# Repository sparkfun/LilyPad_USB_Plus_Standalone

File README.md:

SparkFun LilyPad USB Plus
========================================

[*LilyPad USB Plus (14631)*](https://www.sparkfun.com/products/14631)

This is the LilyPad USB Plus, a sewable electronics microcontroller board controlled by an ATmega32U4 with the Arduino bootloader. 

Repository Contents
-------------------

* **/Documentation** - Data sheets, additional product information
* **/Hardware** - Eagle design files (.brd, .sch)
* **/Production** - Production panel files (.brd)

<b>Note for Linux Users:</b> If you are installing the LilyPad USB Plus in Linux, this document has some specific notes:
<a href="https://github.com/sparkfun/LilyPad_ProtoSnap_Plus/blob/master/Documentation/LinuxInstallation.md">https://github.com/sparkfun/LilyPad_ProtoSnap_Plus/blob/master/Documentation/LinuxInstallation.md</a>.

Documentation
--------------
* **[Library](https://github.com/sparkfun/LilyPad_USB_Plus_Standalone/tree/master/Libraries)** - Arduino library for the LilyPad USB Plus.
* **[Hookup Guide](https://learn.sparkfun.com/tutorials/lilypad-usb-plus-hookup-guide)** - Basic hookup guide for the LilyPad USB Plus.

License Information
-------------------

This product is _**open source**_! 

Please review the LICENSE.md file for license information. 

If you have any questions or concerns on licensing, please contact techsupport@sparkfun.com.

Distributed as-is; no warranty is given.

- Your friends at SparkFun.

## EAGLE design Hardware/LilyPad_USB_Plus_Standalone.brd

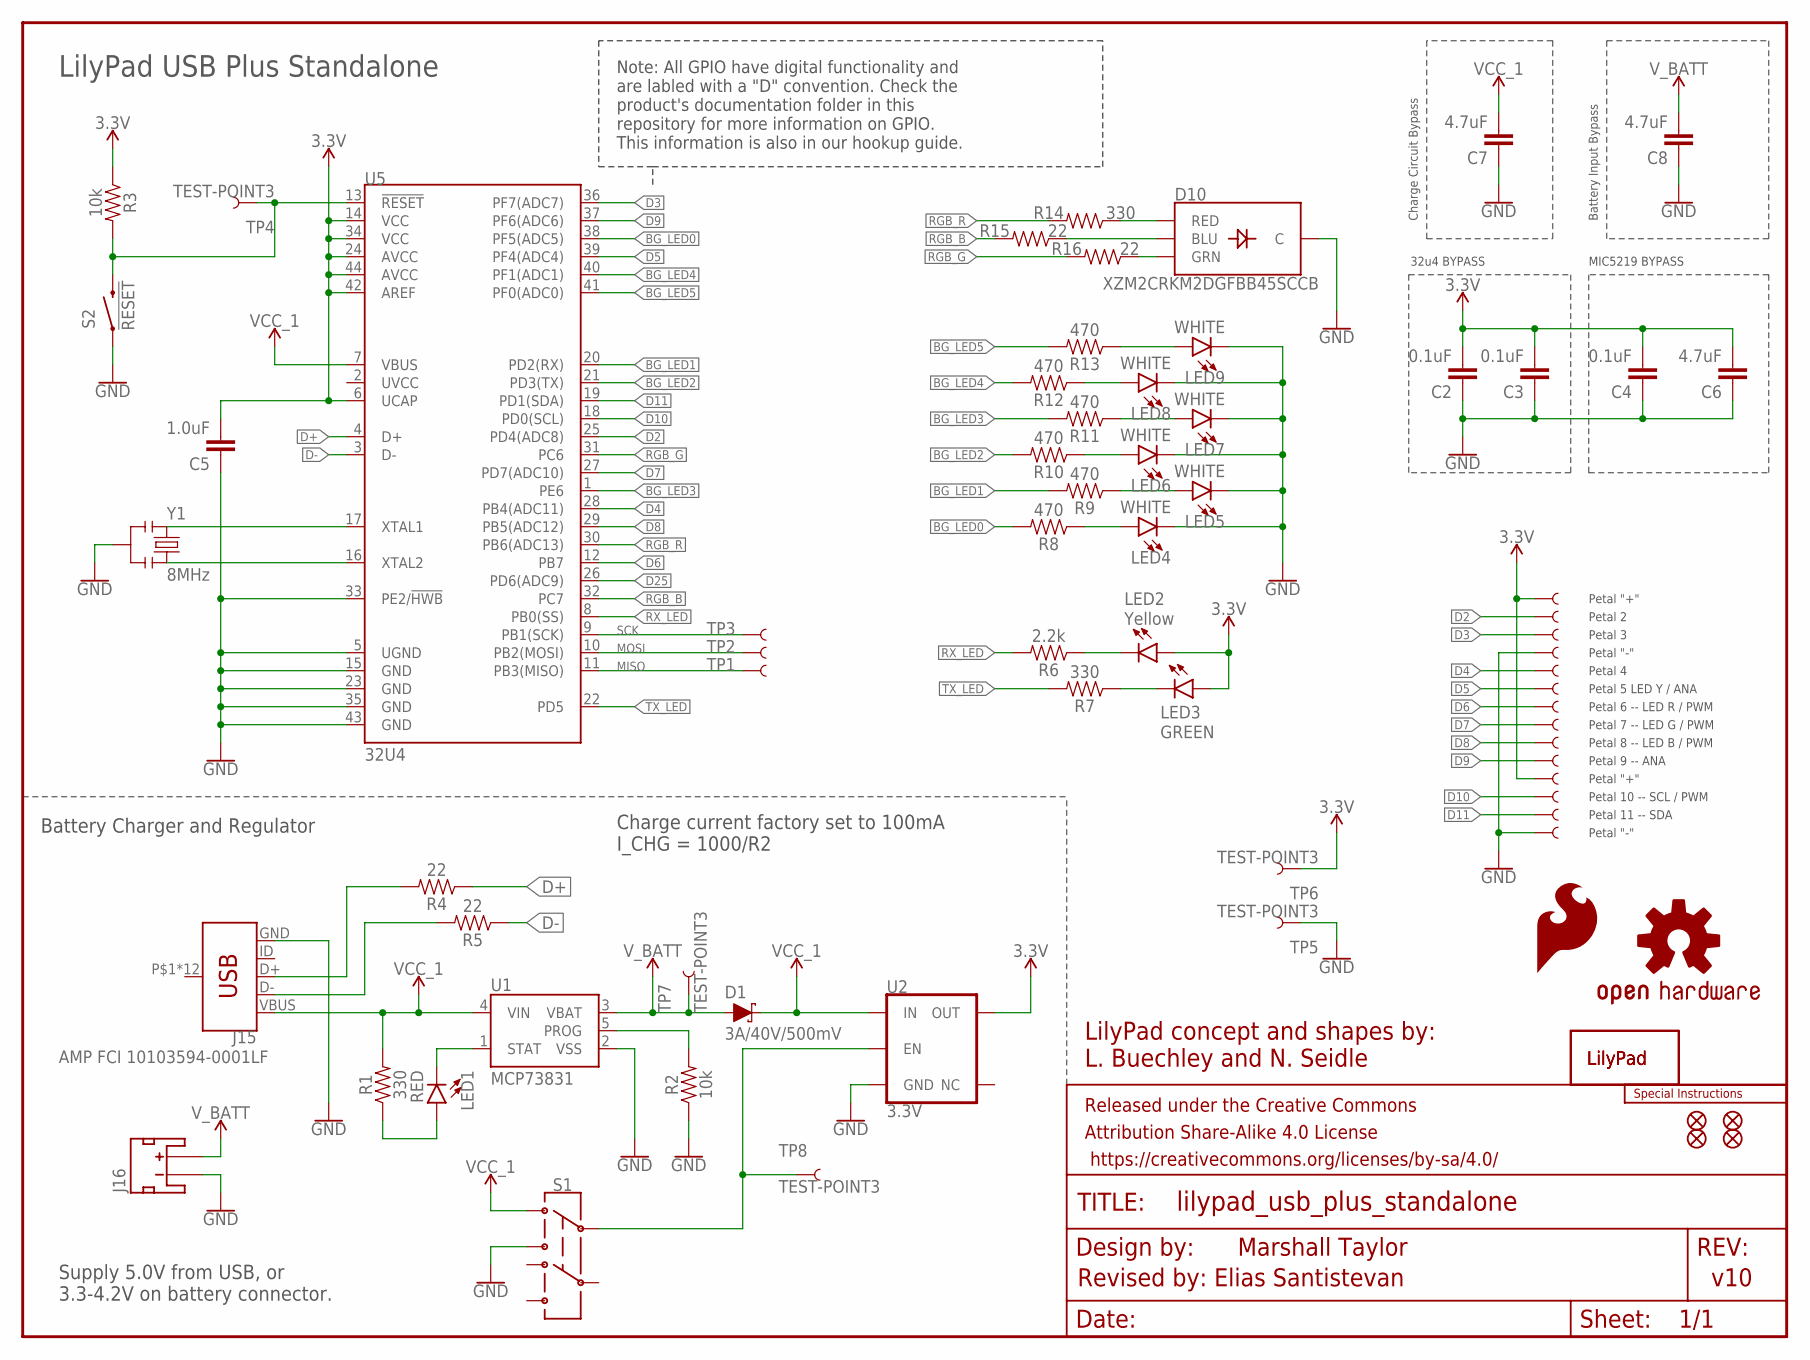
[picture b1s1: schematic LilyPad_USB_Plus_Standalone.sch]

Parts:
C2, C3, C4: 0.1uF; 0402
C5: 1.0uF; 0402
C6, C7, C8: 4.7uF; 0603
D1: 3A/40V/500mV; SMA-DIODE
D10: XZM2CRKM2DGFBB45SCCB; PLCC4SMDLED
FRAME1: FRAME-LETTER; CREATIVE_COMMONS
J1, J2, J3, J4, J5, J6, J7, J8, J9, J10, J11, J12, J13, J14: SEWTAP_LONG-2SIDE; PETAL-LONG-1-2SIDE
J15: AMP FCI 10103594-0001LF; USB-MICROB-PTH
J16: JST_2MM_MALE; JST-2-SMD
JP1, JP2, JP3, JP4: FIDUCIALUFIDUCIAL; MICRO-FIDUCIAL
LED1: RED; LED-0603
LED2: Yellow; LED-0603
LED3: GREEN; LED-0603
LED4, LED5, LED6, LED7, LED8, LED9: WHITE; LED-0603
LOGO1: SFE_LOGO_FLAME.2_INCH; SFE_LOGO_FLAME_.2
LOGO6: OSHW-LOGOS; OSHW-LOGO-S
R1, R7, R14: 330; 0603
R2, R3: 10k; 0603
R4, R5, R15, R16: 22; 0402
R6: 2.2k; 0603
R8, R9, R10, R11, R12, R13: 470; 0402
S1: SWITCH-DPDT-SMD-AYZ0202; SWITCH_DPDT_SMD_AYZ0202
S2: !RESET; TACTILE_SWITCH_SMD_5.2MM
TP1, TP2, TP3, TP4, TP5, TP6, TP7, TP8: TEST-POINT3; PAD.03X.03
U1: MCP73831; SOT23-5
U2: 3.3V; SOT23-5
U5: 32U4; QFN-44-PAD_1:1-LESS_PASTE
U$1, U$13: LILYLOGO_SHORT; LILYPAD-WEARABLES_LOGO-LILYPAD
U$44: SPECIAL_INSTRUCTIONS-ORDERING; ORDERING_INSTRUCTIONS
Y1: 8MHz; RESONATOR-SMD

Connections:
3.3V: C2.2, C3.2, C4.2, C5.2, C6.2, J1.1, J11.1, LED2.A, LED3.A, R3.1, TP6.P$1, U2.5 (OUT), U5.6 (UCAP), U5.14 (VCC), U5.24 (AVCC), U5.34 (VCC), U5.42 (AREF), U5.44 (AVCC)
BG_LED0: R8.2, U5.38 (PF5(ADC5))
BG_LED1: R9.2, U5.20 (PD2(RX))
BG_LED2: R10.2, U5.21 (PD3(TX))
BG_LED3: R11.2, U5.1 (PE6)
BG_LED4: R12.2, U5.40 (PF1(ADC1))
BG_LED5: R13.2, U5.41 (PF0(ADC0))
D2: J2.1, U5.25 (PD4(ADC8))
D3: J3.1, U5.36 (PF7(ADC7))
D4: J5.1, U5.28 (PB4(ADC11))
D5: J6.1, U5.39 (PF4(ADC4))
D6: J7.1, U5.12 (PB7)
D7: J8.1, U5.27 (PD7(ADC10))
D8: J9.1, U5.29 (PB5(ADC12))
D9: J10.1, U5.37 (PF6(ADC6))
D10: J12.1, U5.18 (PD0(SCL))
D11: J13.1, U5.19 (PD1(SDA))
D25: U5.26 (PD6(ADC9))
D+: R4.1, U5.4 (D+)
D-: R5.1, U5.3 (D-)
GND: C2.1, C3.1, C4.1, C5.1, C6.1, C7.1, C8.1, D10.4 (C), J4.1, J14.1, J15.GND, J16.1 (-), LED4.C, LED5.C, LED6.C, LED7.C, LED8.C, LED9.C, R2.1, S1.3, S2.1, S2.2 (1), TP5.P$1, U1.2 (VSS), U2.2 (GND), U5.5 (UGND), U5.15 (GND), U5.23 (GND), U5.33 (PE2/!HWB), U5.35 (GND), U5.43 (GND), Y1.2
MISO: TP1.P$1, U5.11 (PB3(MISO))
MOSI: TP2.P$1, U5.10 (PB2(MOSI))
unnamed: LED2.C, R6.1
unnamed: S1.2, TP8.P$1, U2.3 (EN)
unnamed: LED1.A, R1.1
unnamed: LED1.C, U1.1 (STAT)
unnamed: U5.17 (XTAL1), Y1.1
unnamed: R2.2, U1.5 (PROG)
unnamed: U5.16 (XTAL2), Y1.3
unnamed: D10.2 (GRN), R16.1
unnamed: LED7.A, R11.1
unnamed: LED6.A, R10.1
unnamed: LED5.A, R9.1
unnamed: LED8.A, R12.1
unnamed: LED9.A, R13.1
unnamed: D10.3 (BLU), R15.1
unnamed: D10.1 (RED), R14.1
unnamed: LED4.A, R8.1
unnamed: J15.D-, R5.2
unnamed: J15.D+, R4.2
unnamed: LED3.C, R7.1
RESET: R3.2, S2.3 (2), S2.4 (2), TP4.P$1, U5.13 (!RESET)
RGB_B: R15.2, U5.32 (PC7)
RGB_G: R16.2, U5.31 (PC6)
RGB_R: R14.2, U5.30 (PB6(ADC13))
RX_LED: R6.2, U5.8 (PB0(SS))
SCK: TP3.P$1, U5.9 (PB1(SCK))
TX_LED: R7.2, U5.22 (PD5)
VCC_1: C7.2, D1.C, J15.VBUS, R1.2, S1.1, U1.4 (VIN), U2.1 (IN), U5.7 (VBUS)
V_BATT: C8.2, D1.A, J16.2 (+), TP7.P$1, U1.3 (VBAT)

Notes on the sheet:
32u4 BYPASS
MIC5219 BYPASS
Marshall Taylor
v10
LilyPad concept and shapes by: L. Buechley and N. Seidle
Charge Circuit Bypass
Battery Input Bypass
Petal 2
Petal 3
Petal 4
Petal 5 LED Y / ANA
Petal 6 -- LED R / PWM
Petal 7 -- LED G / PWM
Petal 8 -- LED B / PWM
Petal 9 -- ANA
Petal 10 -- SCL / PWM
Petal 11 -- SDA
Petal "+"
Petal "-"
LilyPad USB Plus Standalone
Battery Charger and Regulator
Charge current factory set to 100mA I_CHG = 1000/R2
Supply 5.0V from USB, or 3.3-4.2V on battery connector.
Revised by: Elias Santistevan
Note: All GPIO have digital functionality and are labled with a "D" convention. Check the product's documentation folder in this repository for more information on GPIO. This information is also in our hookup guide.

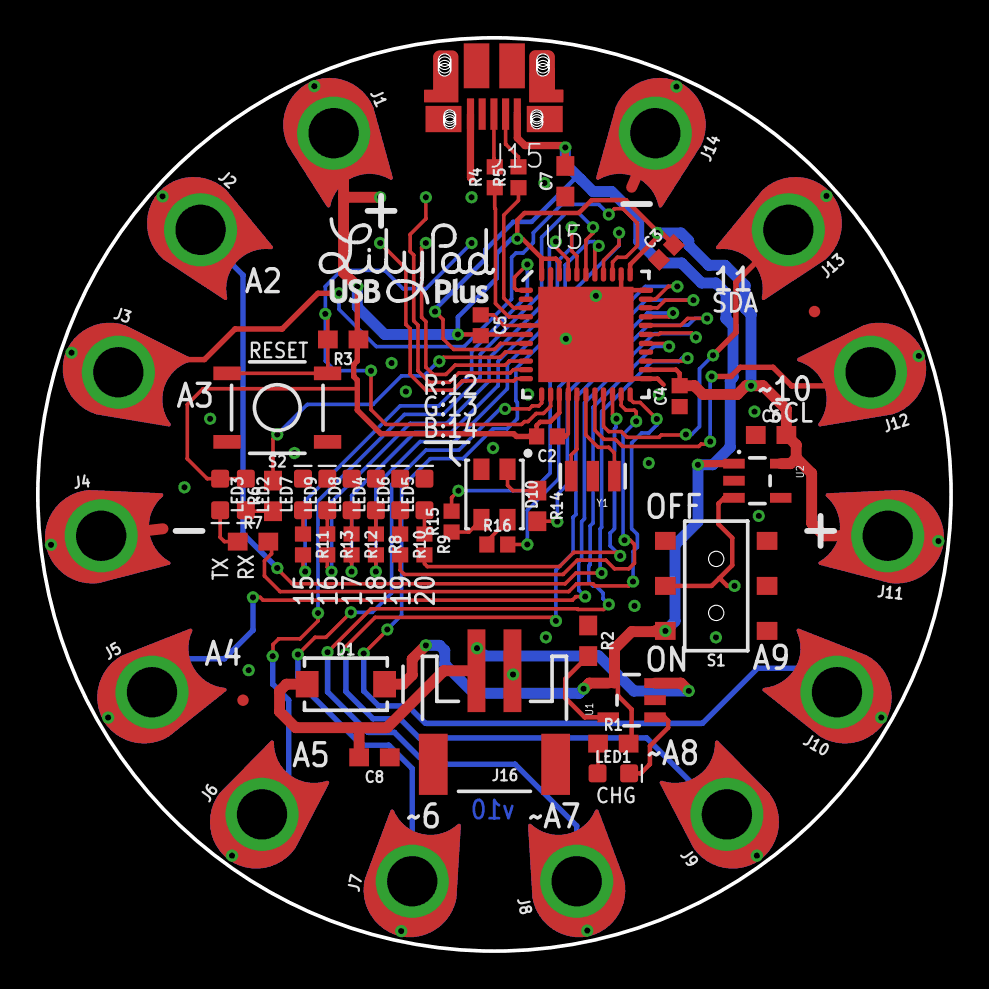
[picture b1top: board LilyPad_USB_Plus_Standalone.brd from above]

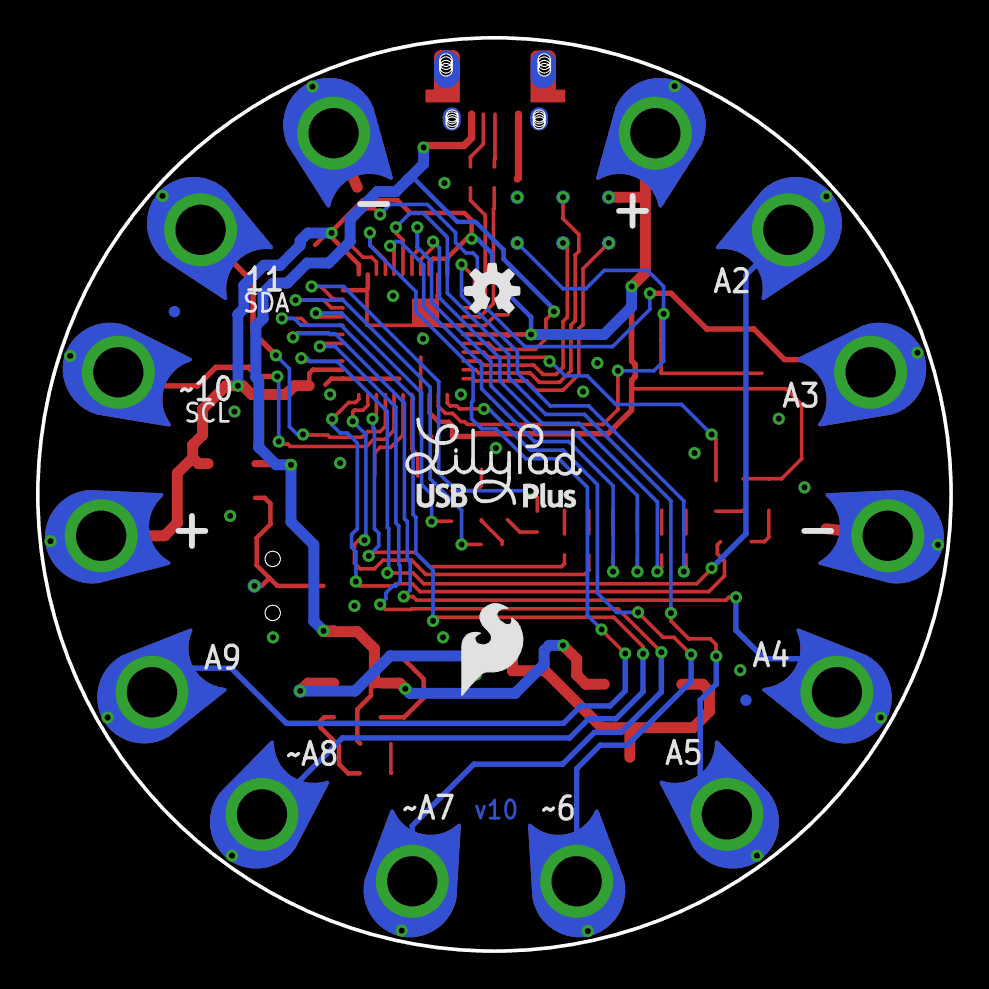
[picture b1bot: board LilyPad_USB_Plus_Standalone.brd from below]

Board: 2 copper layers, 50.7 x 50.7 mm, 101 parts (13 on the bottom side), 50 nets.

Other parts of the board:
U$3, U$9, U$11, U$15, U$17, U$19, U$21, U$23, U$25, U$27, U$29, U$31, U$33, U$34: PETAL_PAD_OFF
U$7, U$8, U$10, U$12, U$16, U$18, U$20, U$22, U$24, U$26, U$28, U$30, U$32: PETAL_SPACE_OFF

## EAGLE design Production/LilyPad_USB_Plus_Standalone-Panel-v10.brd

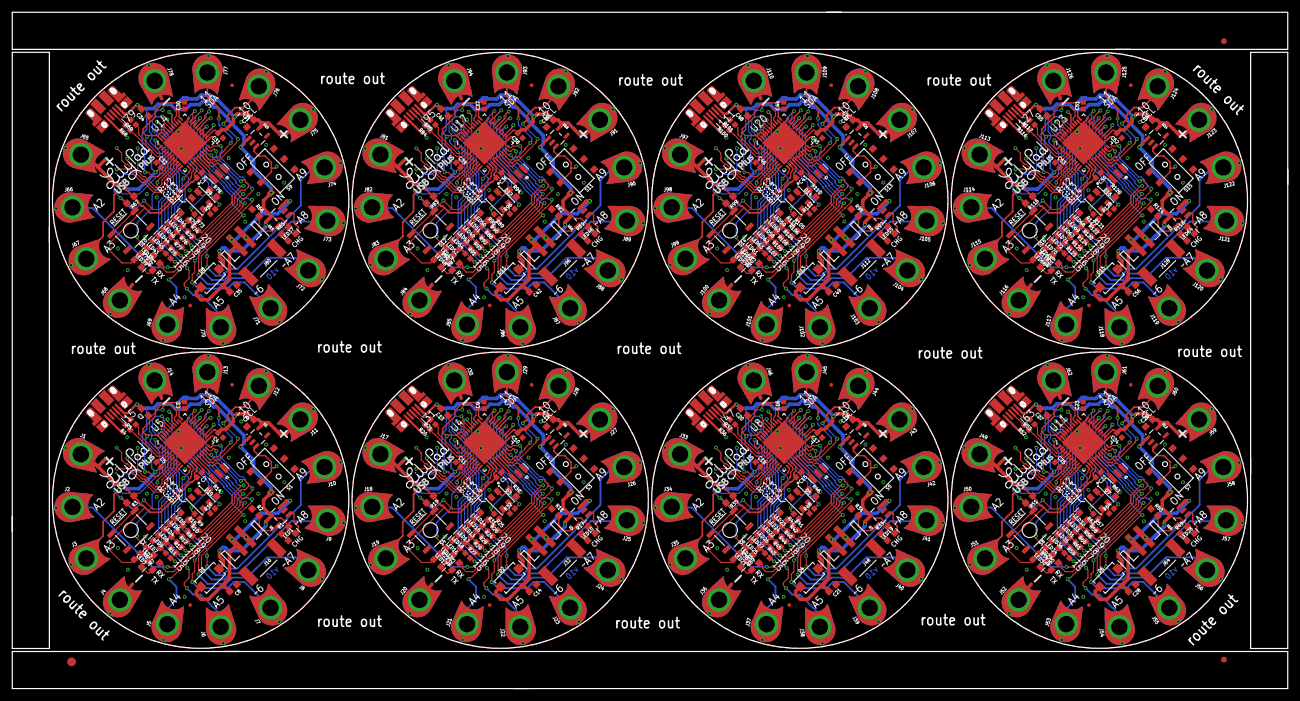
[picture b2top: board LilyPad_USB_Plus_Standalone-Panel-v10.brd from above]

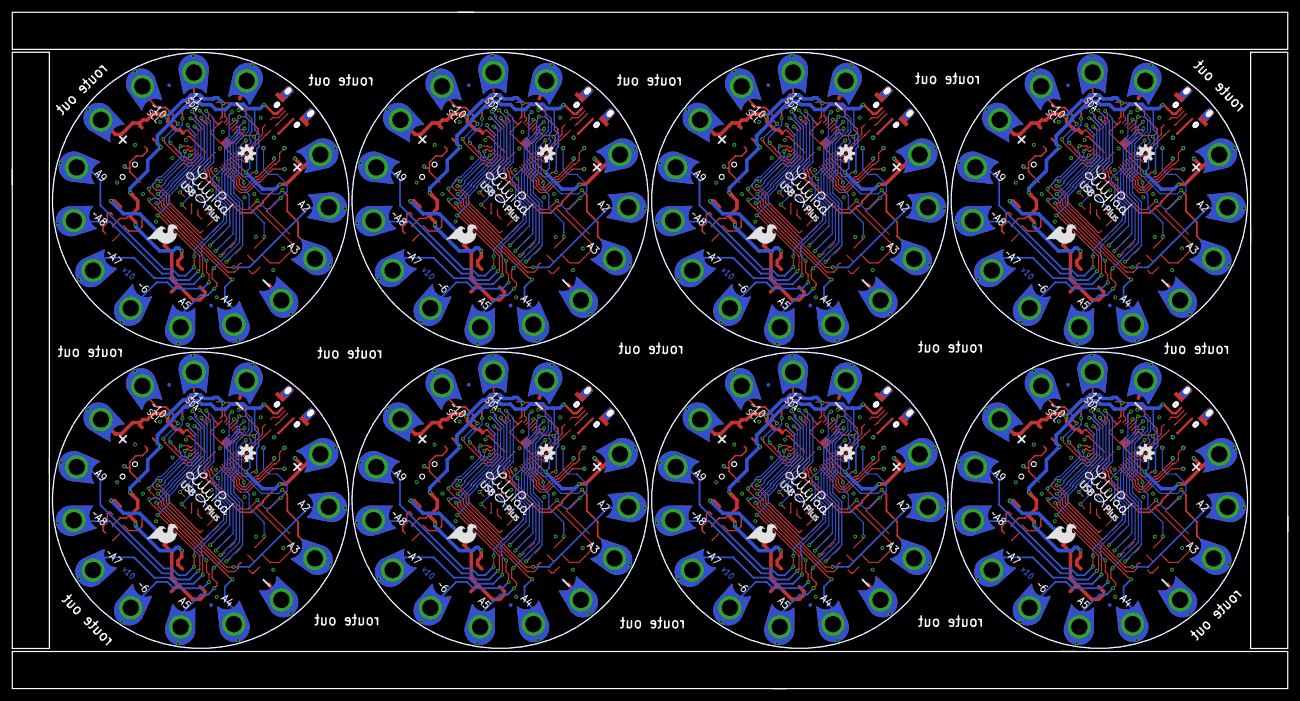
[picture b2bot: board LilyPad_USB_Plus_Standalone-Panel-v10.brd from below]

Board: 2 copper layers, 218.4 x 115.8 mm, 795 parts (104 on the bottom side), 400 nets.

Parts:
C1, C2, C3, C4, C9, C10, C15, C16, C17, C22, C23, C24, C29, C30, C31, C36, C37, C38, C43, C44, C45, C50, C51, C52: 0.1uF; 0402
C5, C11, C18, C25, C32, C39, C46, C53: 1.0uF; 0402
C6, C7, C8, C12, C13, C14, C19, C20, C21, C26, C27, C28, C33, C34, C35, C40, C41, C42, C47, C48, C49, C54, C55, C56: 4.7uF; 0603
D1, D2, D4, D6, D8, D11, D13, D15: 3A/40V/500mV; SMA-DIODE
D3, D5, D7, D9, D10, D12, D14, D16: XZM2CRKM2DGFBB45SCCB; PLCC4SMDLED
E$1: FIDUCIAL-1.5X3
E$5, E$8: FIDUCIAL-1X2
J1, J2, J3, J4, J5, J6, J7, J8, J9, J10, J11, J12, J13, J14, J17, J18, J19, J20, J21, J22, J23, J24, J25, J26, J27, J28, J29, J30, J33, J34, J35, J36, J37, J38, J39, J40, J41, J42, J43, J44, J45, J46, J49, J50, J51, J52, J53, J54, J55, J56, J57, J58, J59, J60, J61, J62, J65, J66, J67, J68, J69, J70, J71, J72, J73, J74, J75, J76, J77, J78, J81, J82, J83, J84, J85, J86, J87, J88, J89, J90, J91, J92, J93, J94, J97, J98, J99, J100, J101, J102, J103, J104, J105, J106, J107, J108, J109, J110, J113, J114, J115, J116, J117, J118, J119, J120, J121, J122, J123, J124, J125, J126: SEWTAP_LONG-2SIDE; PETAL-LONG-1-2SIDE
J15, J31, J47, J63, J79, J95, J111, J127: AMP FCI 10103594-0001LF; USB-MICROB-PTH
J16, J32, J48, J64, J80, J96, J112, J128: JST-2-SMD
JP1, JP2, JP3, JP4, JP5, JP6, JP7, JP8, JP9, JP10, JP11, JP12, JP13, JP14, JP15, JP16, JP17, JP18, JP19, JP20, JP21, JP22, JP23, JP24, JP25, JP26, JP27, JP28, JP29, JP30, JP31, JP32: FIDUCIALUFIDUCIAL; MICRO-FIDUCIAL
LED1, LED10, LED19, LED28, LED37, LED46, LED55, LED64: RED; LED-0603
LED2, LED11, LED20, LED29, LED38, LED47, LED56, LED65: Yellow; LED-0603
LED3, LED12, LED21, LED30, LED39, LED48, LED57, LED66: GREEN; LED-0603
LED4, LED5, LED6, LED7, LED8, LED9, LED13, LED14, LED15, LED16, LED17, LED18, LED22, LED23, LED24, LED25, LED26, LED27, LED31, LED32, LED33, LED34, LED35, LED36, LED40, LED41, LED42, LED43, LED44, LED45, LED49, LED50, LED51, LED52, LED53, LED54, LED58, LED59, LED60, LED61, LED62, LED63, LED67, LED68, LED69, LED70, LED71, LED72: WHITE; LED-0603
LOGO1, LOGO3, LOGO5, LOGO8, LOGO10, LOGO12, LOGO14, LOGO16: SFE_LOGO_FLAME.2_INCH; SFE_LOGO_FLAME_.2
LOGO2, LOGO4, LOGO6, LOGO7, LOGO9, LOGO11, LOGO13, LOGO15: OSHW-LOGOS; OSHW-LOGO-S
R1, R7, R14, R17, R23, R30, R33, R39, R46, R49, R55, R62, R65, R71, R78, R81, R87, R94, R97, R103, R110, R113, R119, R126: 330; 0603
R2, R3, R18, R19, R34, R35, R50, R51, R66, R67, R82, R83, R98, R99, R114, R115: 10k; 0603
R4, R5, R15, R16, R20, R21, R31, R32, R36, R37, R47, R48, R52, R53, R63, R64, R68, R69, R79, R80, R84, R85, R95, R96, R100, R101, R111, R112, R116, R117, R127, R128: 22; 0402
R6, R22, R38, R54, R70, R86, R102, R118: 2.2k; 0603
R8, R9, R10, R11, R12, R13, R24, R25, R26, R27, R28, R29, R40, R41, R42, R43, R44, R45, R56, R57, R58, R59, R60, R61, R72, R73, R74, R75, R76, R77, R88, R89, R90, R91, R92, R93, R104, R105, R106, R107, R108, R109, R120, R121, R122, R123, R124, R125: 470; 0402
S1, S3, S5, S7, S9, S11, S13, S15: SWITCH_DPDT_SMD_AYZ0202
S2, S4, S6, S8, S10, S12, S14, S16: !RESET; TACTILE_SWITCH_SMD_5.2MM
TP1, TP2, TP3, TP4, TP5, TP6, TP7, TP8, TP9, TP10, TP11, TP12, TP13, TP14, TP15, TP16, TP17, TP18, TP19, TP20, TP21, TP22, TP23, TP24, TP25, TP26, TP27, TP28, TP29, TP30, TP31, TP32, TP33, TP34, TP35, TP36, TP37, TP38, TP39, TP40, TP41, TP42, TP43, TP44, TP45, TP46, TP47, TP48, TP49, TP50, TP51, TP52, TP53, TP54, TP55, TP56, TP57, TP58, TP59, TP60, TP61, TP62, TP63, TP64: TEST-POINT3; PAD.03X.03
U1, U3, U7, U10, U13, U16, U19, U22: MCP73831; SOT23-5
U2, U6, U9, U12, U15, U18, U21, U24: 3.3V; SOT23-5
U4, U5, U8, U11, U14, U17, U20, U23: 32U4; QFN-44-PAD_1:1-LESS_PASTE
U$1, U$13, U$57, U$58, U$86, U$87, U$115, U$116, U$144, U$145, U$173, U$174, U$202, U$203, U$231, U$232: LILYLOGO_SHORT; LILYPAD-WEARABLES_LOGO-LILYPAD
U$2, U$3, U$6, U$9, U$11, U$15, U$17, U$19, U$21, U$23, U$25, U$27, U$29, U$31, U$33, U$34, U$35, U$37, U$39, U$41, U$43, U$45, U$47, U$49, U$51, U$53, U$55, U$56, U$59, U$62, U$64, U$66, U$68, U$70, U$72, U$74, U$76, U$78, U$80, U$82, U$84, U$85, U$88, U$91, U$93, U$95, U$97, U$99, U$101, U$103, U$105, U$107, U$109, U$111, U$113, U$114, U$117, U$120, U$122, U$124, U$126, U$128, U$130, U$132, U$134, U$136, U$138, U$140, U$142, U$143, U$146, U$149, U$151, U$153, U$155, U$157, U$159, U$161, U$163, U$165, U$167, U$169, U$171, U$172, U$175, U$178, U$180, U$182, U$184, U$186, U$188, U$190, U$192, U$194, U$196, U$198, U$200, U$201, U$204, U$207, U$209, U$211, U$213, U$215, U$217, U$219, U$221, U$223, U$225, U$227, U$229, U$230: PETAL_PAD_OFF
U$4, U$5, U$7, U$8, U$10, U$12, U$14, U$16, U$18, U$20, U$22, U$24, U$26, U$28, U$30, U$32, U$36, U$38, U$40, U$42, U$44, U$46, U$48, U$50, U$52, U$54, U$60, U$61, U$63, U$65, U$67, U$69, U$71, U$73, U$75, U$77, U$79, U$81, U$83, U$89, U$90, U$92, U$94, U$96, U$98, U$100, U$102, U$104, U$106, U$108, U$110, U$112, U$118, U$119, U$121, U$123, U$125, U$127, U$129, U$131, U$133, U$135, U$137, U$139, U$141, U$147, U$148, U$150, U$152, U$154, U$156, U$158, U$160, U$162, U$164, U$166, U$168, U$170, U$176, U$177, U$179, U$181, U$183, U$185, U$187, U$189, U$191, U$193, U$195, U$197, U$199, U$205, U$206, U$208, U$210, U$212, U$214, U$216, U$218, U$220, U$222, U$224, U$226, U$228: PETAL_SPACE_OFF
Y1, Y2, Y3, Y4, Y5, Y6, Y7, Y8: 8MHz; RESONATOR-SMD

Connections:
3.3V: C2.2, C3.2, C4.2, C5.2, C6.2, J1.1, J11.1, LED2.A, LED3.A, R3.1, TP6.P$1, U2.5, U5.6, U5.14, U5.24, U5.34, U5.42, U5.44
3.3V1: C1.2, C9.2, C10.2, C11.2, C12.2, J17.1, J27.1, LED11.A, LED12.A, R19.1, TP14.P$1, U4.6, U4.14, U4.24, U4.34, U4.42, U4.44, U6.5
3.3V2: C15.2, C16.2, C17.2, C18.2, C19.2, J33.1, J43.1, LED20.A, LED21.A, R35.1, TP22.P$1, U8.6, U8.14, U8.24, U8.34, U8.42, U8.44, U9.5
3.3V3: C22.2, C23.2, C24.2, C25.2, C26.2, J49.1, J59.1, LED29.A, LED30.A, R51.1, TP30.P$1, U11.6, U11.14, U11.24, U11.34, U11.42, U11.44, U12.5
3.3V4: C29.2, C30.2, C31.2, C32.2, C33.2, J65.1, J75.1, LED38.A, LED39.A, R67.1, TP38.P$1, U14.6, U14.14, U14.24, U14.34, U14.42, U14.44, U15.5
3.3V5: C36.2, C37.2, C38.2, C39.2, C40.2, J81.1, J91.1, LED47.A, LED48.A, R83.1, TP46.P$1, U17.6, U17.14, U17.24, U17.34, U17.42, U17.44, U18.5
3.3V6: C43.2, C44.2, C45.2, C46.2, C47.2, J97.1, J107.1, LED56.A, LED57.A, R99.1, TP54.P$1, U20.6, U20.14, U20.24, U20.34, U20.42, U20.44, U21.5
3.3V7: C50.2, C51.2, C52.2, C53.2, C54.2, J113.1, J123.1, LED65.A, LED66.A, R115.1, TP62.P$1, U23.6, U23.14, U23.24, U23.34, U23.42, U23.44, U24.5
BG_LED0: R8.2, U5.38
BG_LED1: R9.2, U5.20
BG_LED2: R10.2, U5.21
BG_LED3: R11.2, U5.1
BG_LED4: R12.2, U5.40
BG_LED5: R13.2, U5.41
BG_LED6: R24.2, U4.38
BG_LED7: R25.2, U4.20
BG_LED8: R26.2, U4.21
BG_LED9: R27.2, U4.1
BG_LED10: R28.2, U4.40
BG_LED11: R29.2, U4.41
BG_LED12: R40.2, U8.38
BG_LED13: R41.2, U8.20
BG_LED14: R42.2, U8.21
BG_LED15: R43.2, U8.1
BG_LED16: R44.2, U8.40
BG_LED17: R45.2, U8.41
BG_LED18: R56.2, U11.38
BG_LED19: R57.2, U11.20
BG_LED20: R58.2, U11.21
BG_LED21: R59.2, U11.1
BG_LED22: R60.2, U11.40
BG_LED23: R61.2, U11.41
BG_LED24: R72.2, U14.38
BG_LED25: R73.2, U14.20
BG_LED26: R74.2, U14.21
BG_LED27: R75.2, U14.1
BG_LED28: R76.2, U14.40
BG_LED29: R77.2, U14.41
BG_LED30: R88.2, U17.38
BG_LED31: R89.2, U17.20
BG_LED32: R90.2, U17.21
BG_LED33: R91.2, U17.1
BG_LED34: R92.2, U17.40
BG_LED35: R93.2, U17.41
BG_LED36: R104.2, U20.38
BG_LED37: R105.2, U20.20
BG_LED38: R106.2, U20.21
BG_LED39: R107.2, U20.1
BG_LED40: R108.2, U20.40
BG_LED41: R109.2, U20.41
BG_LED42: R120.2, U23.38
BG_LED43: R121.2, U23.20
BG_LED44: R122.2, U23.21
BG_LED45: R123.2, U23.1
BG_LED46: R124.2, U23.40
BG_LED47: R125.2, U23.41
D1: J28.1, U4.18
D2: J2.1, U5.25
D3: J3.1, U5.36
D4: J5.1, U5.28
D5: J6.1, U5.39
D6: J7.1, U5.12
D7: J8.1, U5.27
D8: J9.1, U5.29
D9: J10.1, U5.37
D10: J12.1, U5.18
D11: J13.1, U5.19
D12: J23.1, U4.12
D13: J29.1, U4.19
D14: J18.1, U4.25
D16: J24.1, U4.27
D17: J21.1, U4.28
D18: J25.1, U4.29
D19: J19.1, U4.36
D20: J26.1, U4.37
D21: J22.1, U4.39
D22: J44.1, U8.18
D23: J39.1, U8.12
D24: J45.1, U8.19
D26: J34.1, U8.25
D28: J40.1, U8.27
D29: J37.1, U8.28
D30: J41.1, U8.29
D31: J35.1, U8.36
D32: J42.1, U8.37
D33: J38.1, U8.39
D34: J60.1, U11.18
D35: J55.1, U11.12
D36: J61.1, U11.19
D37: J50.1, U11.25
D39: J56.1, U11.27
D40: J53.1, U11.28
D41: J57.1, U11.29
D42: J51.1, U11.36
D43: J58.1, U11.37
D44: J54.1, U11.39
D45: J76.1, U14.18
D46: J71.1, U14.12
D47: J77.1, U14.19
D48: J66.1, U14.25
D50: J72.1, U14.27
D51: J69.1, U14.28
D52: J73.1, U14.29
D53: J67.1, U14.36
D54: J74.1, U14.37
D55: J70.1, U14.39
D56: J92.1, U17.18
D57: J87.1, U17.12
D58: J93.1, U17.19
D59: J82.1, U17.25
D61: J88.1, U17.27
D62: J85.1, U17.28
D63: J89.1, U17.29
D64: J83.1, U17.36
D65: J90.1, U17.37
D66: J86.1, U17.39
D67: J108.1, U20.18
D68: J103.1, U20.12
D69: J109.1, U20.19
D70: J98.1, U20.25
D72: J104.1, U20.27
D73: J101.1, U20.28
D74: J105.1, U20.29
D75: J99.1, U20.36
D76: J106.1, U20.37
D77: J102.1, U20.39
D78: J124.1, U23.18
D79: J119.1, U23.12
D80: J125.1, U23.19
D81: J114.1, U23.25
D83: J120.1, U23.27
D84: J117.1, U23.28
D85: J121.1, U23.29
D86: J115.1, U23.36
D87: J122.1, U23.37
D88: J118.1, U23.39
D+: R4.1, U5.4
D+1: R20.1, U4.4
D+2: R36.1, U8.4
D+3: R52.1, U11.4
D+4: R68.1, U14.4
D+5: R84.1, U17.4
D+6: R100.1, U20.4
D+7: R116.1, U23.4
D-: R5.1, U5.3
D-1: R21.1, U4.3
D-2: R37.1, U8.3
D-3: R53.1, U11.3
D-4: R69.1, U14.3
D-5: R85.1, U17.3
D-6: R101.1, U20.3
D-7: R117.1, U23.3
GND: C2.1, C3.1, C4.1, C5.1, C6.1, C7.1, C8.1, D10.4, J4.1, J14.1, J15.GND, J16.1, LED4.C, LED5.C, LED6.C, LED7.C, LED8.C, LED9.C, R2.1, S1.3, S2.1, S2.2, TP5.P$1, U1.2, U2.2, U5.5, U5.15, U5.23, U5.33, U5.35, U5.43, Y1.2
GND1: C1.1, C9.1, C10.1, C11.1, C12.1, C13.1, C14.1, D3.4, J20.1, J30.1, J31.GND, J32.1, LED13.C, LED14.C, LED15.C, LED16.C, LED17.C, LED18.C, R18.1, S3.3, S4.1, S4.2, TP13.P$1, U3.2, U4.5, U4.15, U4.23, U4.33, U4.35, U4.43, U6.2, Y2.2
GND2: C15.1, C16.1, C17.1, C18.1, C19.1, C20.1, C21.1, D5.4, J36.1, J46.1, J47.GND, J48.1, LED22.C, LED23.C, LED24.C, LED25.C, LED26.C, LED27.C, R34.1, S5.3, S6.1, S6.2, TP21.P$1, U7.2, U8.5, U8.15, U8.23, U8.33, U8.35, U8.43, U9.2, Y3.2
GND3: C22.1, C23.1, C24.1, C25.1, C26.1, C27.1, C28.1, D7.4, J52.1, J62.1, J63.GND, J64.1, LED31.C, LED32.C, LED33.C, LED34.C, LED35.C, LED36.C, R50.1, S7.3, S8.1, S8.2, TP29.P$1, U10.2, U11.5, U11.15, U11.23, U11.33, U11.35, U11.43, U12.2, Y4.2
GND4: C29.1, C30.1, C31.1, C32.1, C33.1, C34.1, C35.1, D9.4, J68.1, J78.1, J79.GND, J80.1, LED40.C, LED41.C, LED42.C, LED43.C, LED44.C, LED45.C, R66.1, S9.3, S10.1, S10.2, TP37.P$1, U13.2, U14.5, U14.15, U14.23, U14.33, U14.35, U14.43, U15.2, Y5.2
GND5: C36.1, C37.1, C38.1, C39.1, C40.1, C41.1, C42.1, D12.4, J84.1, J94.1, J95.GND, J96.1, LED49.C, LED50.C, LED51.C, LED52.C, LED53.C, LED54.C, R82.1, S11.3, S12.1, S12.2, TP45.P$1, U16.2, U17.5, U17.15, U17.23, U17.33, U17.35, U17.43, U18.2, Y6.2
GND6: C43.1, C44.1, C45.1, C46.1, C47.1, C48.1, C49.1, D14.4, J100.1, J110.1, J111.GND, J112.1, LED58.C, LED59.C, LED60.C, LED61.C, LED62.C, LED63.C, R98.1, S13.3, S14.1, S14.2, TP53.P$1, U19.2, U20.5, U20.15, U20.23, U20.33, U20.35, U20.43, U21.2, Y7.2
GND7: C50.1, C51.1, C52.1, C53.1, C54.1, C55.1, C56.1, D16.4, J116.1, J126.1, J127.GND, J128.1, LED67.C, LED68.C, LED69.C, LED70.C, LED71.C, LED72.C, R114.1, S15.3, S16.1, S16.2, TP61.P$1, U22.2, U23.5, U23.15, U23.23, U23.33, U23.35, U23.43, U24.2, Y8.2
MISO: TP1.P$1, U5.11
MISO1: TP9.P$1, U4.11
MISO2: TP17.P$1, U8.11
MISO3: TP25.P$1, U11.11
MISO4: TP33.P$1, U14.11
MISO5: TP41.P$1, U17.11
MISO6: TP49.P$1, U20.11
MISO7: TP57.P$1, U23.11
MOSI: TP2.P$1, U5.10
MOSI1: TP10.P$1, U4.10
MOSI2: TP18.P$1, U8.10
MOSI3: TP26.P$1, U11.10
MOSI4: TP34.P$1, U14.10
MOSI5: TP42.P$1, U17.10
MOSI6: TP50.P$1, U20.10
MOSI7: TP58.P$1, U23.10
unnamed: LED2.C, R6.1
unnamed: S1.2, TP8.P$1, U2.3
unnamed: LED1.A, R1.1
unnamed: LED1.C, U1.1
unnamed: U5.17, Y1.1
unnamed: R2.2, U1.5
unnamed: U5.16, Y1.3
unnamed: D10.2, R16.1
unnamed: LED7.A, R11.1
unnamed: LED6.A, R10.1
unnamed: LED5.A, R9.1
unnamed: LED8.A, R12.1
unnamed: LED9.A, R13.1
unnamed: D10.3, R15.1
unnamed: D10.1, R14.1
unnamed: S3.2, TP16.P$1, U6.3
unnamed: LED10.A, R17.1
unnamed: LED4.A, R8.1
unnamed: J15.D-, R5.2
unnamed: J15.D+, R4.2
unnamed: LED3.C, R7.1
unnamed: LED10.C, U3.1
unnamed: R18.2, U3.5
unnamed: J31.D-, R21.2
unnamed: J31.D+, R20.2
unnamed: LED11.C, R22.1
unnamed: LED12.C, R23.1
unnamed: U4.17, Y2.1
unnamed: U4.16, Y2.3
unnamed: LED13.A, R24.1
unnamed: LED16.A, R27.1
unnamed: LED15.A, R26.1
unnamed: LED14.A, R25.1
unnamed: LED17.A, R28.1
unnamed: LED18.A, R29.1
unnamed: D3.2, R32.1
unnamed: D3.3, R31.1
unnamed: D3.1, R30.1
unnamed: S5.2, TP24.P$1, U9.3
unnamed: LED19.A, R33.1
unnamed: LED19.C, U7.1
unnamed: R34.2, U7.5
unnamed: J47.D-, R37.2
unnamed: J47.D+, R36.2
unnamed: LED20.C, R38.1
unnamed: LED21.C, R39.1
unnamed: U8.17, Y3.1
unnamed: U8.16, Y3.3
unnamed: LED22.A, R40.1
unnamed: LED25.A, R43.1
unnamed: LED24.A, R42.1
unnamed: LED23.A, R41.1
unnamed: LED26.A, R44.1
unnamed: LED27.A, R45.1
unnamed: D5.2, R48.1
unnamed: D5.3, R47.1
unnamed: D5.1, R46.1
unnamed: S7.2, TP32.P$1, U12.3
unnamed: LED28.A, R49.1
unnamed: LED28.C, U10.1
unnamed: R50.2, U10.5
unnamed: J63.D-, R53.2
unnamed: J63.D+, R52.2
unnamed: LED29.C, R54.1
unnamed: LED30.C, R55.1
unnamed: U11.17, Y4.1
unnamed: U11.16, Y4.3
unnamed: LED31.A, R56.1
unnamed: LED34.A, R59.1
unnamed: LED33.A, R58.1
unnamed: LED32.A, R57.1
unnamed: LED35.A, R60.1
unnamed: LED36.A, R61.1
unnamed: D7.2, R64.1
unnamed: D7.3, R63.1
unnamed: D7.1, R62.1
unnamed: S9.2, TP40.P$1, U15.3
unnamed: LED37.A, R65.1
unnamed: LED37.C, U13.1
unnamed: R66.2, U13.5
unnamed: J79.D-, R69.2
unnamed: J79.D+, R68.2
unnamed: LED38.C, R70.1
unnamed: LED39.C, R71.1
unnamed: U14.17, Y5.1
unnamed: U14.16, Y5.3
unnamed: LED40.A, R72.1
unnamed: LED43.A, R75.1
unnamed: LED42.A, R74.1
unnamed: LED41.A, R73.1
unnamed: LED44.A, R76.1
unnamed: LED45.A, R77.1
unnamed: D9.2, R80.1
unnamed: D9.3, R79.1
unnamed: D9.1, R78.1
unnamed: S11.2, TP48.P$1, U18.3
unnamed: LED46.A, R81.1
unnamed: LED46.C, U16.1
unnamed: R82.2, U16.5
unnamed: J95.D-, R85.2
unnamed: J95.D+, R84.2
unnamed: LED47.C, R86.1
unnamed: LED48.C, R87.1
unnamed: U17.17, Y6.1
unnamed: U17.16, Y6.3
unnamed: LED49.A, R88.1
unnamed: LED52.A, R91.1
unnamed: LED51.A, R90.1
unnamed: LED50.A, R89.1
unnamed: LED53.A, R92.1
unnamed: LED54.A, R93.1
unnamed: D12.2, R96.1
unnamed: D12.3, R95.1
unnamed: D12.1, R94.1
unnamed: S13.2, TP56.P$1, U21.3
unnamed: LED55.A, R97.1
unnamed: LED55.C, U19.1
unnamed: R98.2, U19.5
unnamed: J111.D-, R101.2
unnamed: J111.D+, R100.2
unnamed: LED56.C, R102.1
unnamed: LED57.C, R103.1
unnamed: U20.17, Y7.1
unnamed: U20.16, Y7.3
unnamed: LED58.A, R104.1
unnamed: LED61.A, R107.1
unnamed: LED60.A, R106.1
unnamed: LED59.A, R105.1
unnamed: LED62.A, R108.1
unnamed: LED63.A, R109.1
unnamed: D14.2, R112.1
unnamed: D14.3, R111.1
unnamed: D14.1, R110.1
unnamed: S15.2, TP64.P$1, U24.3
unnamed: LED64.A, R113.1
unnamed: LED64.C, U22.1
unnamed: R114.2, U22.5
unnamed: J127.D-, R117.2
unnamed: J127.D+, R116.2
unnamed: LED65.C, R118.1
unnamed: LED66.C, R119.1
unnamed: U23.17, Y8.1
unnamed: U23.16, Y8.3
unnamed: LED67.A, R120.1
unnamed: LED70.A, R123.1
unnamed: LED69.A, R122.1
unnamed: LED68.A, R121.1
unnamed: LED71.A, R124.1
unnamed: LED72.A, R125.1
unnamed: D16.2, R128.1
unnamed: D16.3, R127.1
unnamed: D16.1, R126.1
RESET: R3.2, S2.3, S2.4, TP4.P$1, U5.13
RESET1: R19.2, S4.3, S4.4, TP12.P$1, U4.13
RESET2: R35.2, S6.3, S6.4, TP20.P$1, U8.13
RESET3: R51.2, S8.3, S8.4, TP28.P$1, U11.13
RESET4: R67.2, S10.3, S10.4, TP36.P$1, U14.13
RESET5: R83.2, S12.3, S12.4, TP44.P$1, U17.13
RESET6: R99.2, S14.3, S14.4, TP52.P$1, U20.13
RESET7: R115.2, S16.3, S16.4, TP60.P$1, U23.13
RGB_B: R15.2, U5.32
RGB_B1: R31.2, U4.32
RGB_B2: R47.2, U8.32
RGB_B3: R63.2, U11.32
RGB_B4: R79.2, U14.32
RGB_B5: R95.2, U17.32
RGB_B6: R111.2, U20.32
RGB_B7: R127.2, U23.32
RGB_G: R16.2, U5.31
RGB_G1: R32.2, U4.31
RGB_G2: R48.2, U8.31
RGB_G3: R64.2, U11.31
RGB_G4: R80.2, U14.31
RGB_G5: R96.2, U17.31
RGB_G6: R112.2, U20.31
RGB_G7: R128.2, U23.31
RGB_R: R14.2, U5.30
RGB_R1: R30.2, U4.30
RGB_R2: R46.2, U8.30
RGB_R3: R62.2, U11.30
RGB_R4: R78.2, U14.30
RGB_R5: R94.2, U17.30
RGB_R6: R110.2, U20.30
RGB_R7: R126.2, U23.30
RX_LED: R6.2, U5.8
RX_LED1: R22.2, U4.8
RX_LED2: R38.2, U8.8
RX_LED3: R54.2, U11.8
RX_LED4: R70.2, U14.8
RX_LED5: R86.2, U17.8
RX_LED6: R102.2, U20.8
RX_LED7: R118.2, U23.8
SCK: TP3.P$1, U5.9
SCK1: TP11.P$1, U4.9
SCK2: TP19.P$1, U8.9
SCK3: TP27.P$1, U11.9
SCK4: TP35.P$1, U14.9
SCK5: TP43.P$1, U17.9
SCK6: TP51.P$1, U20.9
SCK7: TP59.P$1, U23.9
TX_LED: R7.2, U5.22
TX_LED1: R23.2, U4.22
TX_LED2: R39.2, U8.22
TX_LED3: R55.2, U11.22
TX_LED4: R71.2, U14.22
TX_LED5: R87.2, U17.22
TX_LED6: R103.2, U20.22
TX_LED7: R119.2, U23.22
VCC_1: C7.2, D1.C, J15.VBUS, R1.2, S1.1, U1.4, U2.1, U5.7
VCC_2: C13.2, D2.C, J31.VBUS, R17.2, S3.1, U3.4, U4.7, U6.1
VCC_3: C20.2, D4.C, J47.VBUS, R33.2, S5.1, U7.4, U8.7, U9.1
VCC_4: C27.2, D6.C, J63.VBUS, R49.2, S7.1, U10.4, U11.7, U12.1
VCC_5: C34.2, D8.C, J79.VBUS, R65.2, S9.1, U13.4, U14.7, U15.1
VCC_6: C41.2, D11.C, J95.VBUS, R81.2, S11.1, U16.4, U17.7, U18.1
VCC_7: C48.2, D13.C, J111.VBUS, R97.2, S13.1, U19.4, U20.7, U21.1
VCC_8: C55.2, D15.C, J127.VBUS, R113.2, S15.1, U22.4, U23.7, U24.1
V_BATT: C8.2, D1.A, J16.2, TP7.P$1, U1.3
V_BATT1: C14.2, D2.A, J32.2, TP15.P$1, U3.3
V_BATT2: C21.2, D4.A, J48.2, TP23.P$1, U7.3
V_BATT3: C28.2, D6.A, J64.2, TP31.P$1, U10.3
V_BATT4: C35.2, D8.A, J80.2, TP39.P$1, U13.3
V_BATT5: C42.2, D11.A, J96.2, TP47.P$1, U16.3
V_BATT6: C49.2, D13.A, J112.2, TP55.P$1, U19.3
V_BATT7: C56.2, D15.A, J128.2, TP63.P$1, U22.3

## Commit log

2018-02-12 Cleaned up some things
    Ready for proto review
2018-02-21 Small changes after Review
2018-02-22 Issues found from my double check
    Fiducials on underside placed, Sparkfun name on board changed to flame according to Lilypad design rules.
2018-03-02 Fixed issues from double check
2018-03-07 Updated schematic
    Added a note for the user to clarify net naming convention and a GPIO table to the documentation folder for even further clarification.
2018-03-30 Post designe review changes
2018-03-30 Changes after double check
2018-04-05 created panel v10
2018-05-22 Updating Readme with available links
    Hookup guide, sku, etc
2018-06-08 Updating read me with libraries link
    Updating read me with libraries link
2018-06-08 Deleting empty folders
    Nothing in Enclosure, Firmware, Libraries, Software
2018-06-08 Updating readme with deleted folders
    Nothing in Enclosure, Firmware, Libraries, Software

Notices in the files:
parts and their libraries:
SparkFun-PowerIC: Licensing: CC v3.0 Share-Alike You are welcome to use this library for commercial purposes.
SparkFun-Aesthetics: Released under the Creative Commons Attribution Share-Alike 4.0 License
SparkFun-Aesthetics: https://creativecommons.org/licenses/by-sa/4.0
